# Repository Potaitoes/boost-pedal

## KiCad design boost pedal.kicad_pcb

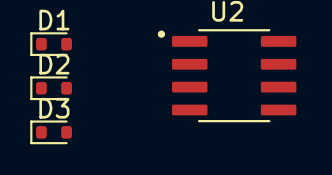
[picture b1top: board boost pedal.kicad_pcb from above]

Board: 2 copper layers, 4 parts (0 on the bottom side), 3 nets, no tracks yet.

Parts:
D1, D2, D3: 1N4148WT; D_SOD-523
U2: LMC7660IMX_NOPB; SOIC127P599X175-8N

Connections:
GND: U2.3 (GND), U2.7 (LV)
unnamed: D1.2 (A), D2.1 (K)
unnamed: D1.1 (K), D2.2 (A), D3.1 (K)

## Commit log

2026-02-11 Completed boost design
